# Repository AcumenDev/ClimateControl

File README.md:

# ClimateControl
Климат контроль на Arduino

Библиотеки:
 * LedControl 1.0.6
 * DHT sensor library 1.2.3

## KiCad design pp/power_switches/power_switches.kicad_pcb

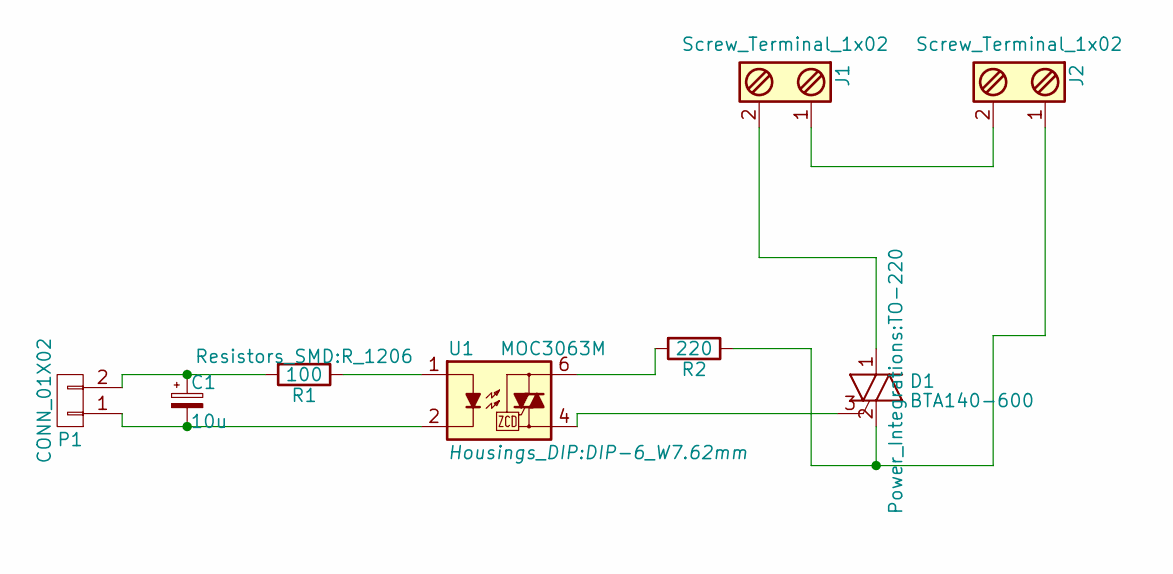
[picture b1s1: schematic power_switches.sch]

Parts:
C1: 10u; CP_Radial_D5.0mm_P2.50mm
D1: BTA140-600; TO-220
J1, J2: Screw_Terminal_1x02; TerminalBlock_Pheonix_MPT-2.54mm_2pol
P1: CONN_01X02; Socket_Strip_Straight_1x02_Pitch2.54mm
R1: 100; R_1206
R2: 220; R_1206
U1: MOC3063M; DIP-6_W7.62mm

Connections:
unnamed: C1.1, P1.2, R1.2
unnamed: C1.2, P1.1, U1.2
unnamed: D1.1 (A1), J1.2
unnamed: D1.2 (A2), J2.1, R2.1
unnamed: D1.3 (G), U1.4
unnamed: J1.1, J2.2
unnamed: R1.1, U1.1
unnamed: R2.2, U1.6

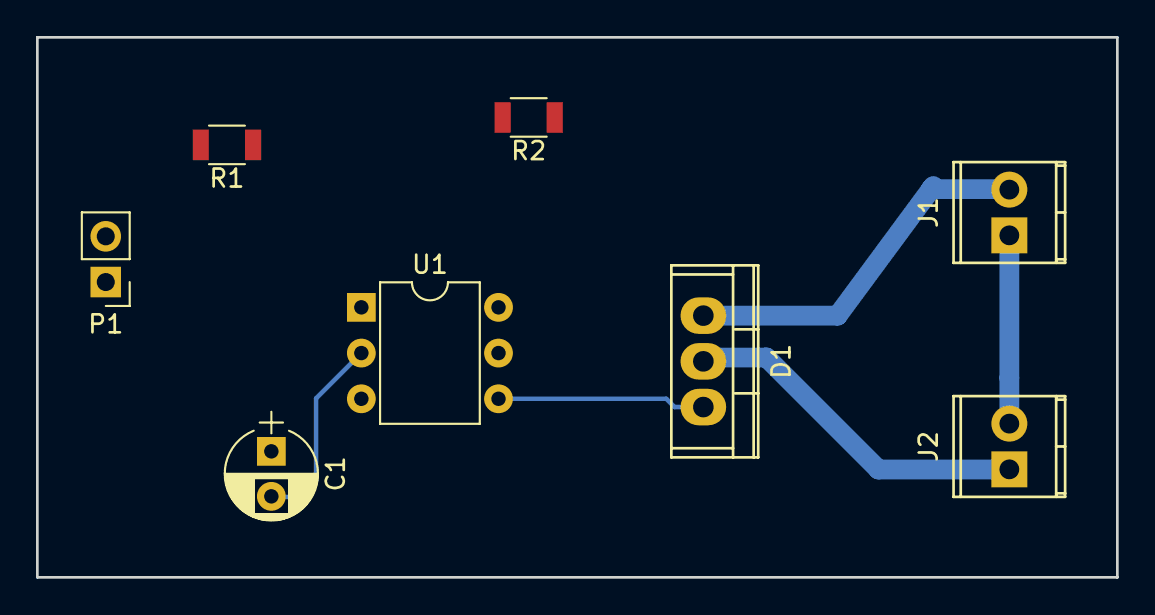
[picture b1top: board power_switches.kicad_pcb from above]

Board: 2 copper layers, 60.0 x 30.0 mm, 8 parts (0 on the bottom side), 8 nets.

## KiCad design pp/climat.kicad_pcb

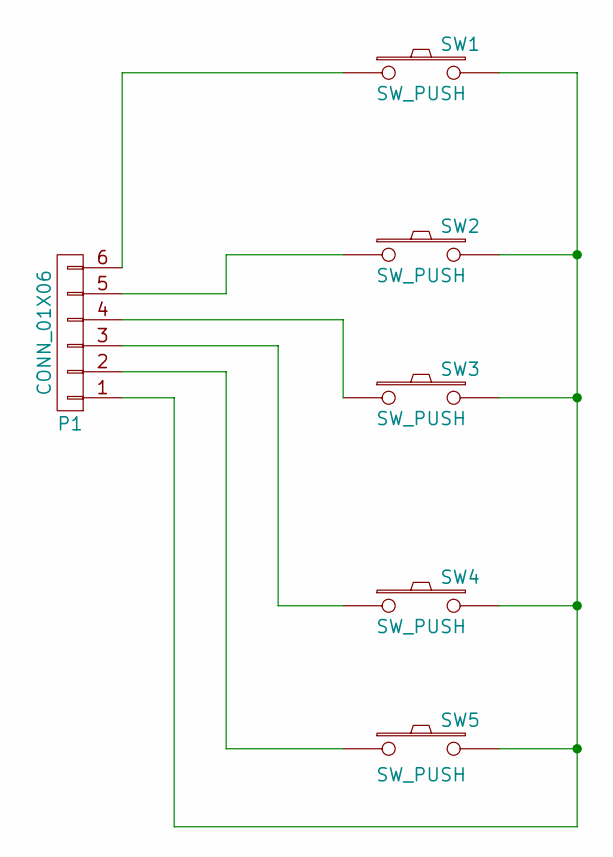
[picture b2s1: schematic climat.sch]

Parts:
P1: CONN_01X06; Pin_Header_Straight_1x06
SW1, SW2, SW3, SW4, SW5: SW_PUSH; SW_PUSH_SMALL

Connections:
unnamed: P1.1, SW1.2, SW2.2, SW3.2, SW4.2, SW5.2
unnamed: P1.2, SW5.1
unnamed: P1.3, SW4.1
unnamed: P1.4, SW3.1
unnamed: P1.5, SW2.1
unnamed: P1.6, SW1.1

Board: 2 copper layers, 6 parts (0 on the bottom side), 6 nets, no tracks yet.

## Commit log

2016-12-18 первая версия климат контроля тесты, заготовка печатной платы
2016-12-18 удалил сылки на либы
2016-12-24 Акамуляция значений, правки багов, скрипт рендеринга графика работы
2016-12-25 Переинициализация дисплея
2017-01-07 Гисериз в 1 процент для влажности, фикс деления на 0, тайм аут при включениии лигики чтобы не звенела релюхами
2017-03-30 Тестирование датчика co2
2017-04-02 Начало реализации новой версии
2017-04-09 Контроль за co2
2017-04-21 вывод на три индикатора, 3-х кнопочное управление, сохранение значений
2017-04-22 Получение данных с датчика co2
2017-04-25 Работа с пид регулятором
2017-05-21 Управление исполнительными устройствами
2017-05-27 Отладка алгоритма
2017-05-28 Доводка алгоритма
2017-05-28 реорганизация папок
2017-06-05 Управление реле
2017-06-09 тесты
2017-06-25 Возврат к релейному управлению
2017-06-26 воскрешение реле
2017-06-29 Поменял пины
2017-07-02 Разогрев датчика co2
2017-07-05 Простенький фильтр
2017-07-15 Начал рисовать схему на симисторах
2017-10-09 силовые ключи
2017-10-22 Тест системы меню
